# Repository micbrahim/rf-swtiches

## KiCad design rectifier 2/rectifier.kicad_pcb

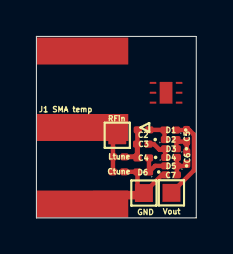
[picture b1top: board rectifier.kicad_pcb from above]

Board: 2 copper layers, 8.9 x 10.1 mm, 19 parts (0 on the bottom side), 9 nets.

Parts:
C2, C3, C4: 33 pF; C_0201_0603Metric
C5, C6, C7: C_Small; C_0201_0603Metric
Ctune: C_tune; C_0201_0603Metric
D1, D2, D3, D4, D5, D6: D_Schottky_Small; D_0201_0603Metric
GND: GND; TestPoint_Pad_1.0x1.0mm
J1 SMA temp: SMA; SMA_Amphenol_132289_EdgeMount
Ltune: L_tune; L_0201_0603Metric
REF: SKY13314-374LF
RFin: TestPoint; TestPoint_Pad_1.0x1.0mm
Vout: Vout; TestPoint_Pad_1.0x1.0mm

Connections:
GND: C7.2, Ctune.1, D6.2 (A), GND.1, J1 SMA temp.2 (Ext)
unnamed: Ctune.2, J1 SMA temp.1 (In), Ltune.1, RFin.1
unnamed: C2.1, D1.2 (A), D2.1 (K)
unnamed: C2.2, C3.2, C4.2, Ltune.2
unnamed: C3.1, D3.2 (A), D4.1 (K)
unnamed: C4.1, D5.2 (A), D6.1 (K)
unnamed: C5.1, D1.1 (K), Vout.1
unnamed: C5.2, C6.1, D2.2 (A), D3.1 (K)
unnamed: C6.2, C7.1, D4.2 (A), D5.1 (K)

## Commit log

2024-06-02 init
2024-06-11 added switches
2024-06-11 added arduino file
2024-09-26 added mosfet
